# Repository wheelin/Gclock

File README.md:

# Gclock

Kicad design files for a ST SensorTile based pocket clock.

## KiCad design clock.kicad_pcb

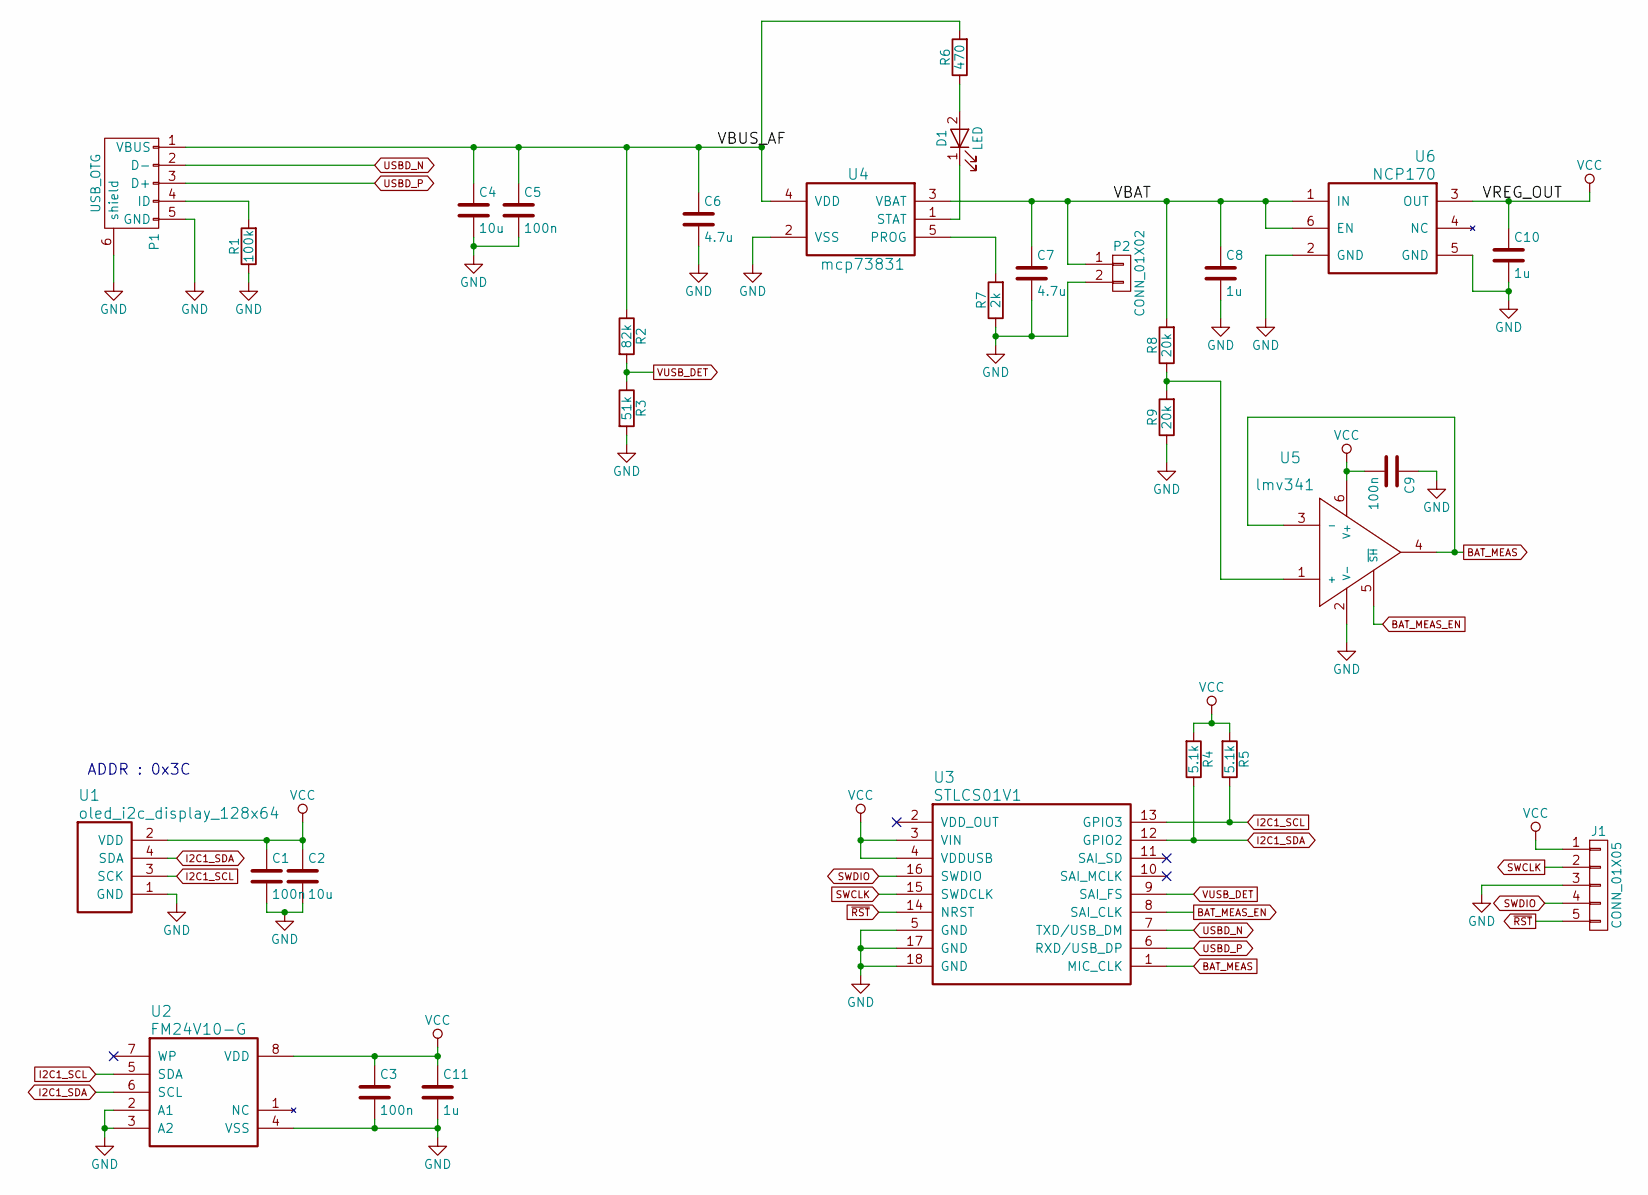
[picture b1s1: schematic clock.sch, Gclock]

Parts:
C1, C3, C5, C9: 100n; C_0402
C2, C4: 10u; C_0402
C6, C7: 4.7u; C_0402
C8, C10, C11: 1u; C_0402
D1: LED; LED_0603
J1: CONN_01X05; Pin_Header_Straight_1x05_Pitch1.27mm
P1: USB_OTG; USB_Micro-B_Molex_47346-0001
P2: CONN_01X02; Pin_Header_Straight_1x02_Pitch2.54mm
R1: 100k; R_0402
R2: 82k; R_0402
R3: 51k; R_0402
R4, R5: 5.1k; R_0402
R6: 470; R_0402
R7: 2k; R_0402
R8, R9: 20k; R_0402
U1: oled_i2c_display_128x64; oled_display
U2: FM24V10-G; SOIC-8_3.9x4.9mm_Pitch1.27mm
U3: STLCS01V1; STLC01V1
U4: mcp73831; SOT-23-5
U5: lmv341; SOT-23-6
U6: NCP170; SOT-563

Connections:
/VBAT: C7.1, C8.1, P2.1, R8.2, U4.3 (VBAT), U6.1 (IN), U6.6 (EN)
/VBUS_AF: C4.1, C5.1, C6.1, P1.1 (VBUS), R2.1, R6.2, U4.4 (VDD)
BAT_MEAS: U3.1 (MIC_CLK), U5.3 (-), U5.4
BAT_MEAS_EN: U3.8 (SAI_CLK), U5.5 (~SH)
GND: C1.2, C2.2, C3.2, C4.2, C5.2, C6.2, C7.2, C8.2, C9.1, C10.2, C11.2, J1.3, P1.5 (GND), P1.6 (shield), P2.2, R1.1, R3.2, R7.1, R9.1, U1.1 (GND), U2.2 (A1), U2.3 (A2), U2.4 (VSS), U3.5 (GND), U3.17 (GND), U3.18 (GND), U4.2 (VSS), U5.2 (V-), U6.2 (GND), U6.5 (GND)
I2C1_SCL: R5.1, U1.3 (SCK), U2.5 (SDA), U3.13 (GPIO3)
I2C1_SDA: R4.1, U1.4 (SDA), U2.6 (SCL), U3.12 (GPIO2)
unnamed: D1.1 (K), U4.1 (STAT)
unnamed: D1.2 (A), R6.1
unnamed: P1.4 (ID), R1.2
unnamed: R7.2, U4.5 (PROG)
unnamed: R8.1, R9.2, U5.1 (+)
SWCLK: J1.2, U3.15 (SWDCLK)
SWDIO: J1.4, U3.16 (SWDIO)
USBD_N: P1.2 (D-), U3.7 (TXD/USB_DM)
USBD_P: P1.3 (D+), U3.6 (RXD/USB_DP)
VCC: C1.1, C2.1, C3.1, C9.2, C10.1, C11.1, J1.1, R4.2, R5.2, U1.2 (VDD), U2.8 (VDD), U3.3 (VIN), U3.4 (VDDUSB), U5.6 (V+), U6.3 (OUT)
VUSB_DET: R2.2, R3.1, U3.9 (SAI_FS)
~RST: J1.5, U3.14 (NRST)

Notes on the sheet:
ADDR : 0x3C

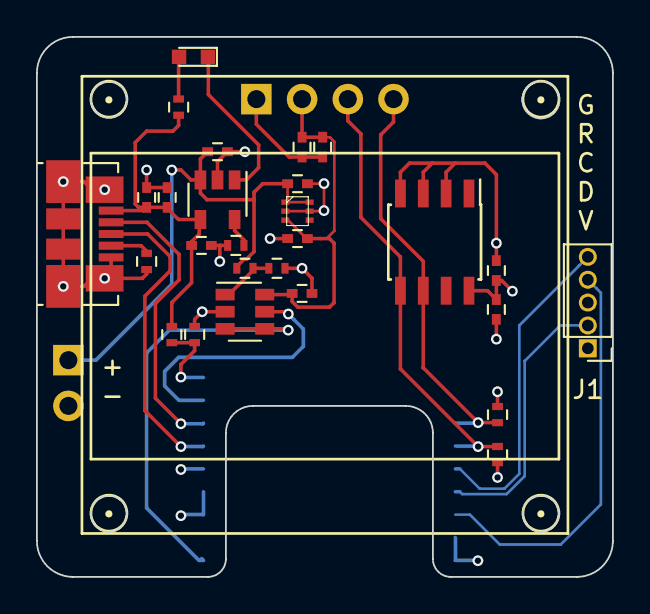
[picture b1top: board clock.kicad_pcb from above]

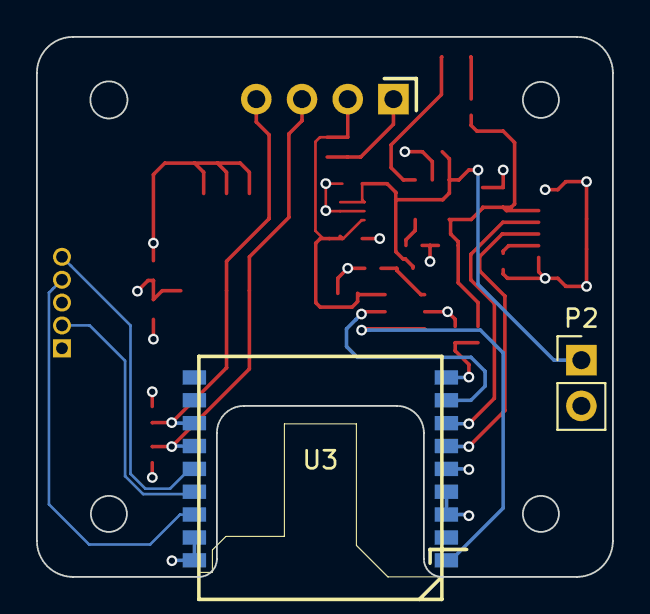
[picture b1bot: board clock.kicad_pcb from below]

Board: 4 copper layers, 32.0 x 30.0 mm, 30 parts (2 on the bottom side), 19 nets.

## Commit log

2017-08-18 added image of the pcb
2017-08-18 added pdf schematic and changed some opts in sch
2017-08-19 modified ncp170 symbol because was totally wrong, F%*ç%
2017-08-19 small modif
